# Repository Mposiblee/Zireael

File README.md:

# Zireael keyboard

Zireael is an ergonomic wireless split keyboard with a design bias. Keyboard for Kailh Choc switches based on MINEW MS88SF2 BLE module.

The keyboard is based on Dao Chok BLE. The locations of components on the board have been changed, space for the battery has been added, and the thumb cluster has also been changed.

Inspiration for the keyboard was taken from these keyboards:
- [Dao chok BLE](https://github.com/yumagulovrn/dao-choc-ble) by [Rafael](https://github.com/yumagulovrn) - components pcb
- [Corne-ish Zen](https://lowprokb.ca/products/corne-ish-zen) by [DarrylDH](https://github.com/LOWPROKB) - the idea to create a beautiful case
- [Cornelius](https://geekhack.org/index.php?topic=109741.0) by [foostan](https://github.com/foostan) - keyboard view

## Features

- Hotswapabble
- ZMK firmware
- Low profile
- Top mount
- Choc Spacing (18mm x 17mm)

## Firmware

Latest compiled ZMK firmware for this keyboard can be found here: https://github.com/Mposiblee/zireael-zmk-config/releases/tag/firmware

Source Code: https://github.com/Mposiblee/zireael-zmk-config

## Build guide

https://github.com/Mposiblee/Zireael/blob/main/doc/build_guide.md

## Contacts

Telegram channel: https://t.me/mposibl

My telegram: https://t.me/mposible

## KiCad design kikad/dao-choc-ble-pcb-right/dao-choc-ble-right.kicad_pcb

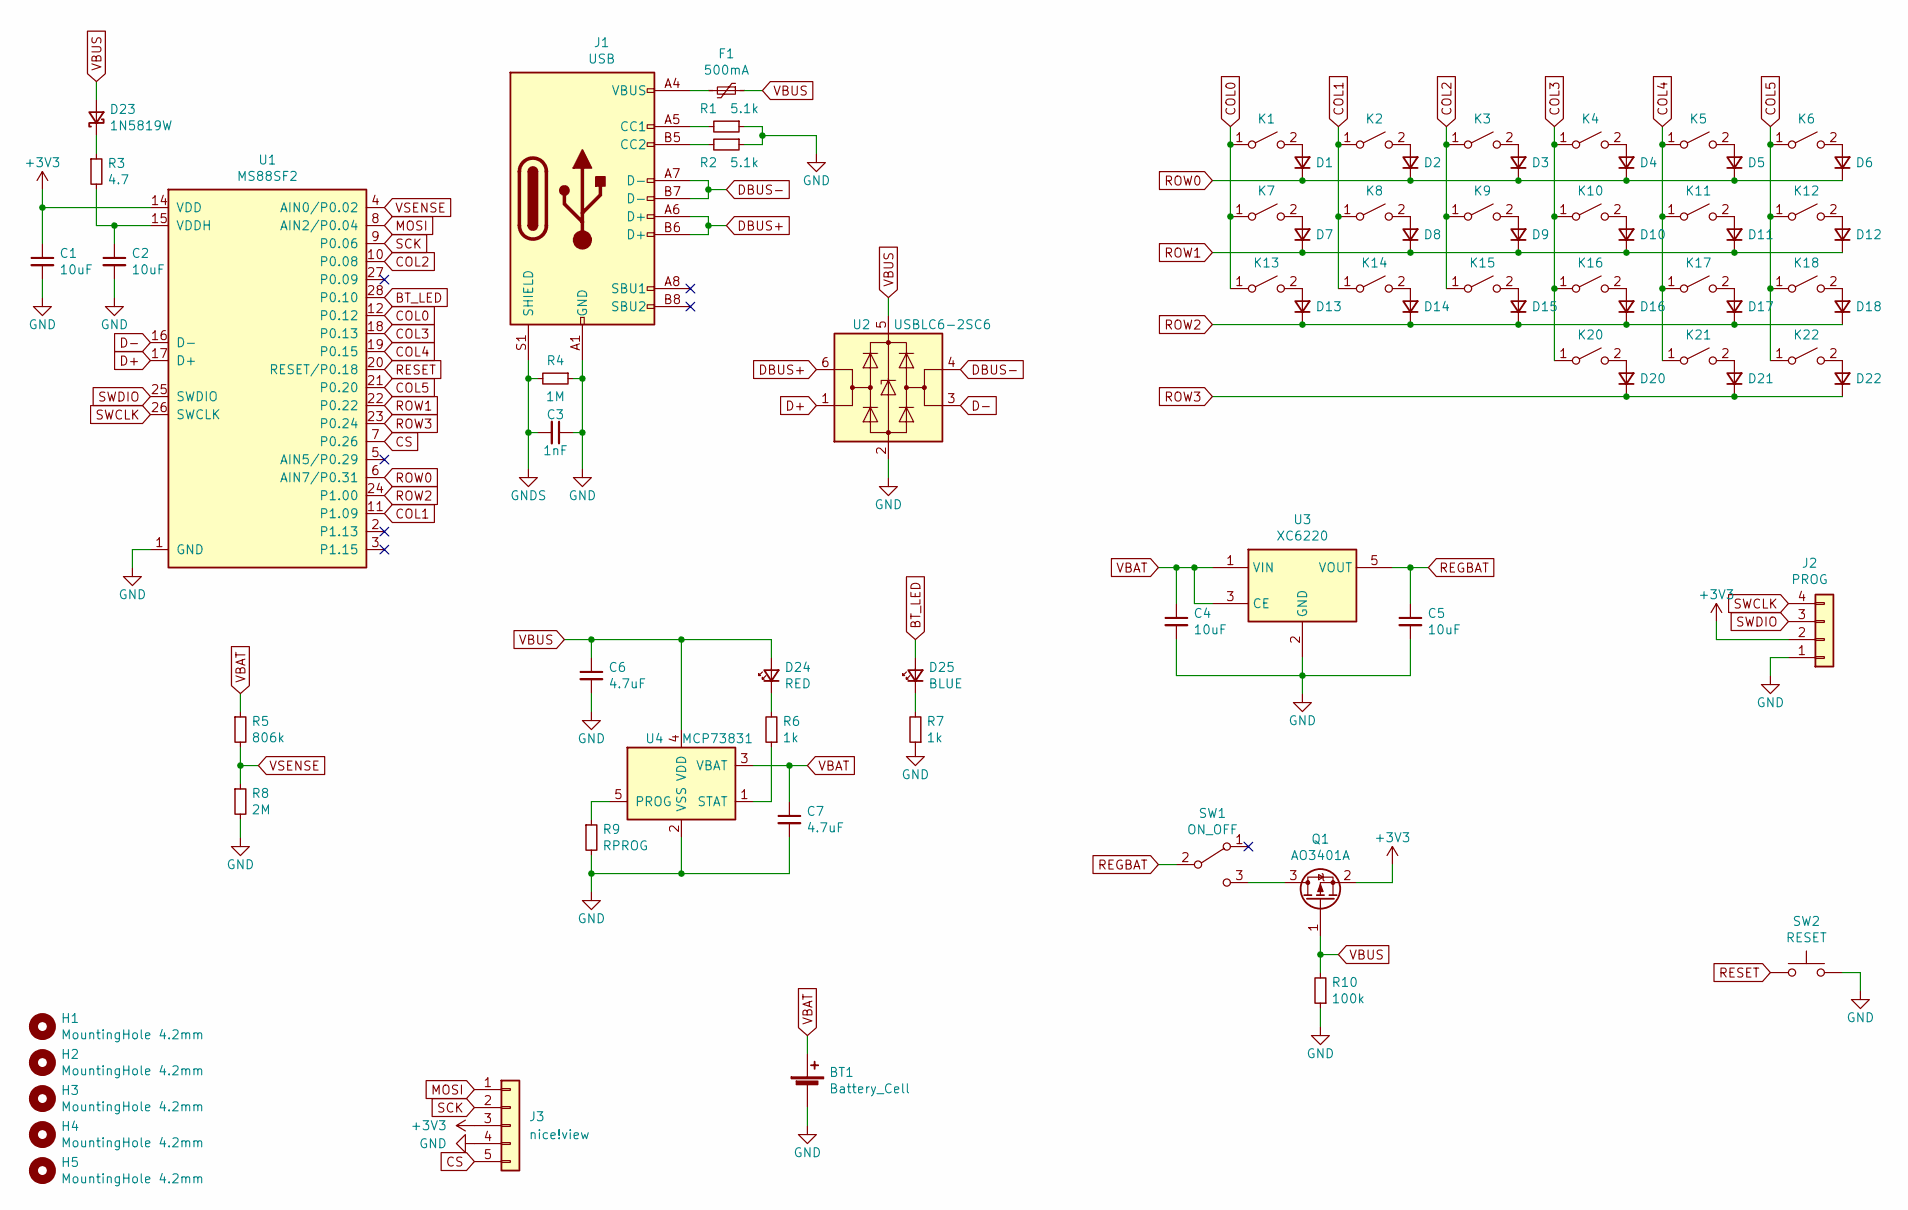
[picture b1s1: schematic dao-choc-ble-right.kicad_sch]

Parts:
BT1: Battery_Cell; Battery
C1, C2, C4, C5: 10uF; C_0603_1608Metric; LCSC C19702
C3: 1nF; C_0603_1608Metric; LCSC C1588
C6, C7: 4.7uF; C_0603_1608Metric; LCSC C19666
D1, D2, D3, D4, D5, D6, D7, D8, D9, D10, D11, D12, D13, D14, D15, D16, D17, D18, D20, D21, D22: 1N4148WS; D_SOD-323; LCSC C57759
D23: 1N5819W; D_SOD-523; LCSC C169540
D24: RED; LED_0603_1608Metric; LCSC C2286
D25: BLUE; LED_0603_1608Metric; LCSC C72041
F1: 500mA; Fuse_1206_3216Metric; LCSC C355568
H1, H2, H3, H4, H5: MountingHole 4.2mm; Hole_4.2mm
J1: USB; USB-C_C168688; LCSC C168688
J2: PROG
J3: nice!view
K1, K2, K3, K4, K5, K6, K7, K8, K9, K10, K11, K12, K13, K14, K15, K16, K17, K18, K20, K21, K22: KEY_SWITCH; Kailh_PG1350_hotswap
Q1: AO3401A; SOT-23; LCSC C15127
R1, R2: 5.1k; R_0603_1608Metric; LCSC C23186
R3: 4.7; R_0603_1608Metric; LCSC C23164
R4: 1M; R_0603_1608Metric; LCSC C22935
R5: 806k; R_0603_1608Metric; LCSC C103828
R6, R7: 1k; R_0603_1608Metric; LCSC C21190
R8: 2M; R_0603_1608Metric; LCSC C22976
R9: RPROG; R_0603_1608Metric; LCSC C22978
R10: 100k; R_0603_1608Metric; LCSC C25803
SW1: ON_OFF; MSK-12C02; LCSC C431541
SW2: RESET; TS-1086E; LCSC C455276
U1: MS88SF2; MINEW_MS88SF2
U2: USBLC6-2SC6; SOT-23-6; LCSC C558442
U3: XC6220; SOT-23-5; LCSC C86534
U4: MCP73831; SOT-23-5; LCSC C14879

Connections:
+3V3: C1.1, J2.2, J3.3, Q1.2 (S), U1.14 (VDD)
BT_LED: D25.2 (A), U1.28 (P0.10)
COL0: K1.1 (A), K7.1 (A), K13.1 (A), U1.12 (P0.12)
COL1: K2.1 (A), K8.1 (A), K14.1 (A), U1.11 (P1.09)
COL2: K3.1 (A), K9.1 (A), K15.1 (A), U1.10 (P0.08)
COL3: K4.1 (A), K10.1 (A), K16.1 (A), K20.1 (A), U1.18 (P0.13)
COL4: K5.1 (A), K11.1 (A), K17.1 (A), K21.1 (A), U1.19 (P0.15)
COL5: K6.1 (A), K12.1 (A), K18.1 (A), K22.1 (A), U1.21 (P0.20)
CS: J3.5, U1.7 (P0.26)
D+: U1.17 (D+), U2.1 (I/O1)
D-: U1.16 (D-), U2.3 (I/O2)
DBUS+: J1.A6 (D+), J1.B6 (D+), U2.6 (I/O1)
DBUS-: J1.A7 (D-), J1.B7 (D-), U2.4 (I/O2)
GND: BT1.2 (-), C1.2, C2.2, C3.1, C4.2, C5.2, C6.2, C7.2, J1.A1 (GND), J1.A12 (GND), J1.B1 (GND), J1.B12 (GND), J2.1, J3.4, R1.1, R2.1, R4.1, R7.1, R8.2, R9.2, R10.1, SW2.2, U1.1 (GND), U1.13 (GND), U2.2 (GND), U3.2 (GND), U4.2 (VSS)
GNDS: C3.2, J1.S1 (SHIELD), R4.2
MOSI: J3.1, U1.8 (AIN2/P0.04)
unnamed: C2.1, R3.2, U1.15 (VDDH)
unnamed: D1.2 (A), K1.2 (B)
unnamed: D2.2 (A), K2.2 (B)
unnamed: D3.2 (A), K3.2 (B)
unnamed: D4.2 (A), K4.2 (B)
unnamed: D5.2 (A), K5.2 (B)
unnamed: D6.2 (A), K6.2 (B)
unnamed: D7.2 (A), K7.2 (B)
unnamed: D8.2 (A), K8.2 (B)
unnamed: D9.2 (A), K9.2 (B)
unnamed: D10.2 (A), K10.2 (B)
unnamed: D11.2 (A), K11.2 (B)
unnamed: D12.2 (A), K12.2 (B)
unnamed: D13.2 (A), K13.2 (B)
unnamed: D14.2 (A), K14.2 (B)
unnamed: D15.2 (A), K15.2 (B)
unnamed: D16.2 (A), K16.2 (B)
unnamed: D17.2 (A), K17.2 (B)
unnamed: D18.2 (A), K18.2 (B)
unnamed: D20.2 (A), K20.2 (B)
unnamed: D21.2 (A), K21.2 (B)
unnamed: D22.2 (A), K22.2 (B)
unnamed: D23.1 (K), R3.1
unnamed: D24.1 (K), R6.2
unnamed: D25.1 (K), R7.2
unnamed: F1.2, J1.A4 (VBUS), J1.A9 (VBUS), J1.B4 (VBUS), J1.B9 (VBUS)
unnamed: J1.A5 (CC1), R1.2
unnamed: J1.B5 (CC2), R2.2
unnamed: Q1.3 (D), SW1.3 (C)
unnamed: R6.1, U4.1 (STAT)
unnamed: R9.1, U4.5 (PROG)
REGBAT: C5.1, SW1.2 (B), U3.5 (VOUT)
RESET: SW2.1, U1.20 (RESET/P0.18)
ROW0: D1.1 (K), D2.1 (K), D3.1 (K), D4.1 (K), D5.1 (K), D6.1 (K), U1.6 (AIN7/P0.31)
ROW1: D7.1 (K), D8.1 (K), D9.1 (K), D10.1 (K), D11.1 (K), D12.1 (K), U1.22 (P0.22)
ROW2: D13.1 (K), D14.1 (K), D15.1 (K), D16.1 (K), D17.1 (K), D18.1 (K), U1.24 (P1.00)
ROW3: D20.1 (K), D21.1 (K), D22.1 (K), U1.23 (P0.24)
SCK: J3.2, U1.9 (P0.06)
SWCLK: J2.4, U1.26 (SWCLK)
SWDIO: J2.3, U1.25 (SWDIO)
VBAT: BT1.1 (+), C4.1, C7.1, R5.1, U3.1 (VIN), U3.3 (CE), U4.3 (VBAT)
VBUS: C6.1, D23.2 (A), D24.2 (A), F1.1, Q1.1 (G), R10.2, U2.5 (VBUS), U4.4 (VDD)
VSENSE: R5.2, R8.1, U1.4 (AIN0/P0.02)

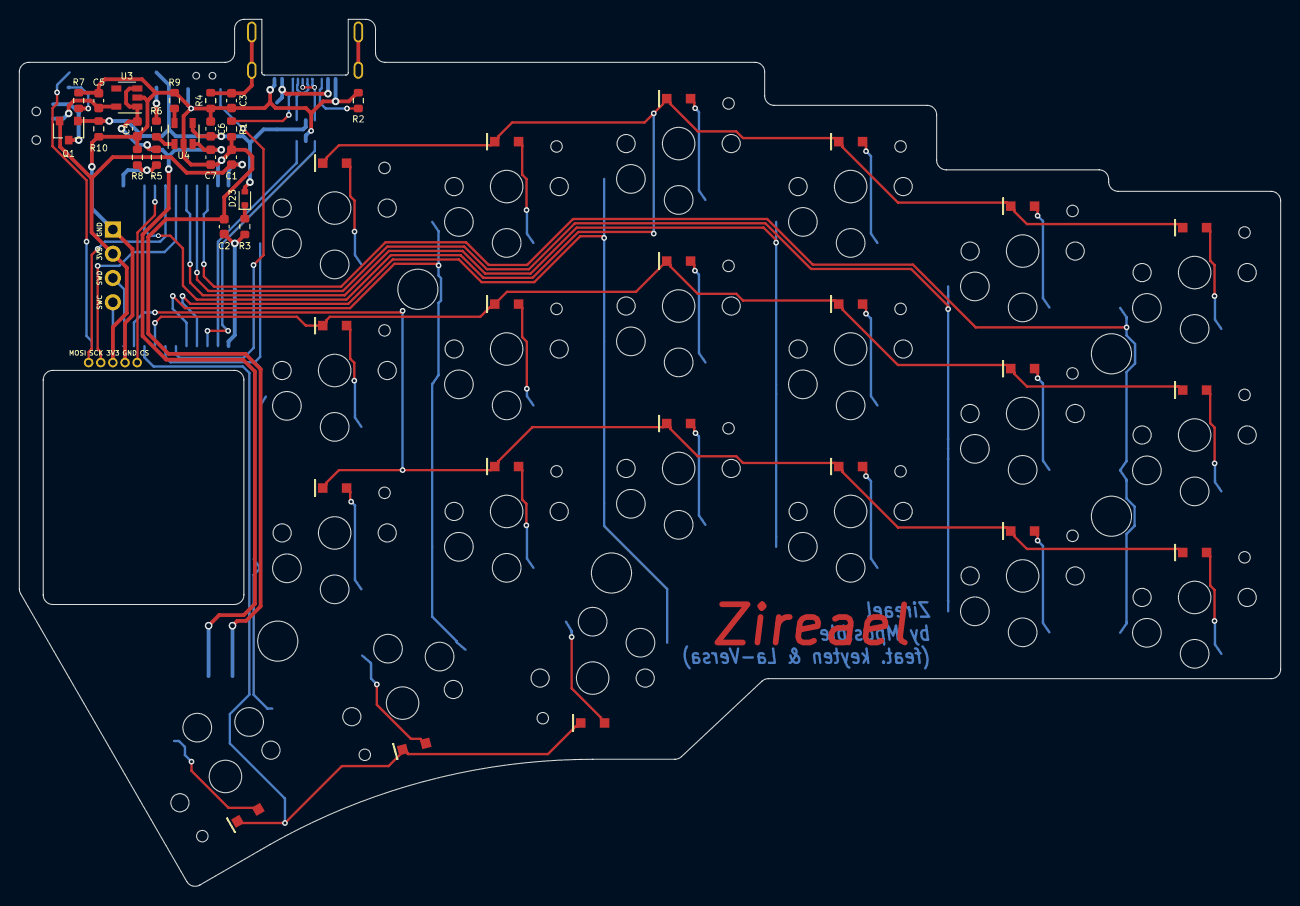
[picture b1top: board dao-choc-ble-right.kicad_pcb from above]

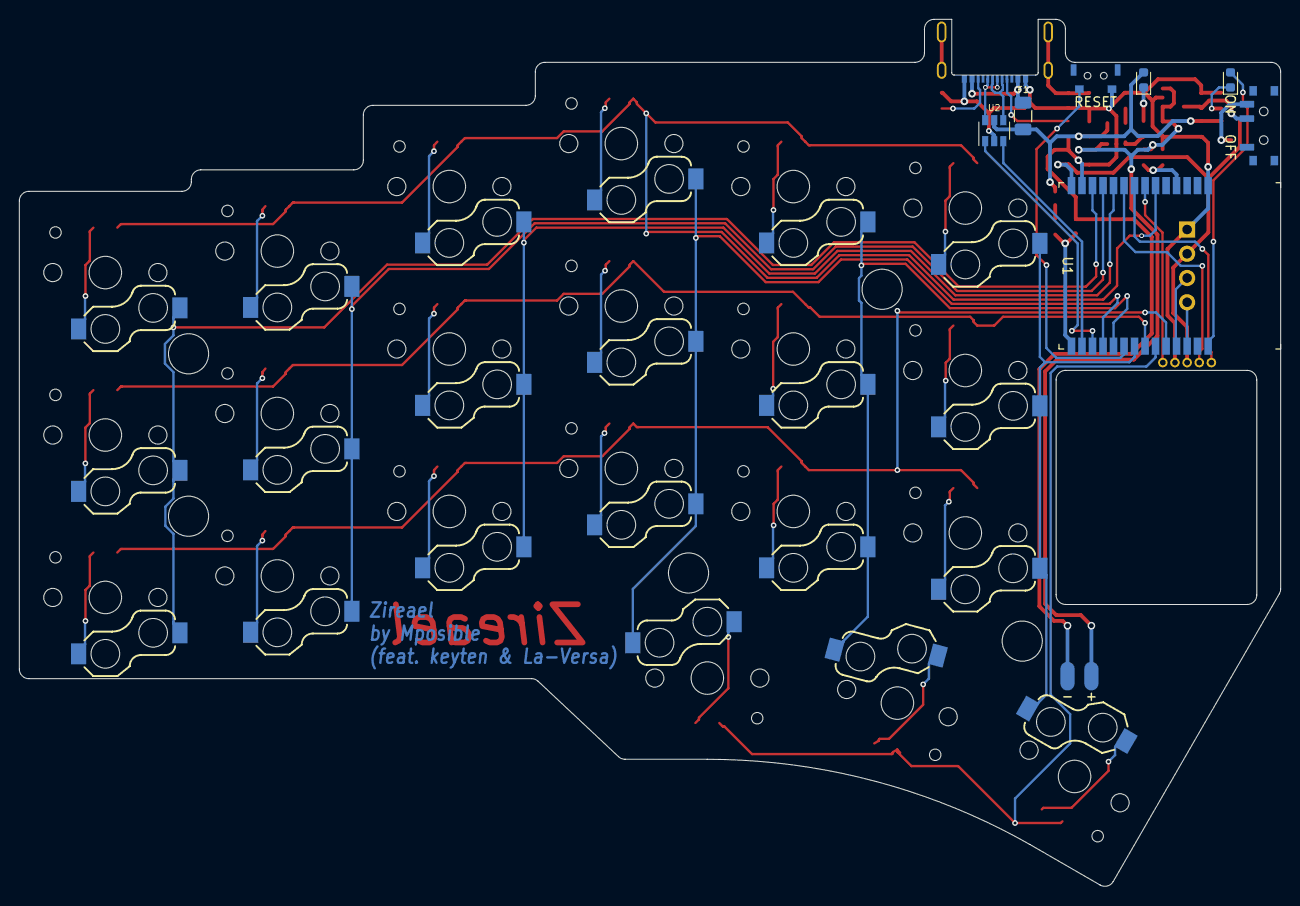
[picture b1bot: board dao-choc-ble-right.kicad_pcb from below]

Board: 2 copper layers, 132.0 x 90.7 mm, 79 parts (9 on the bottom side), 59 nets.

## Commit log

2023-11-07 photos
2023-11-07 Create photos
2023-11-07 Create jpg
2023-11-07 Create fdsa
2023-11-07 Create stl
2023-11-07 Rename stl to sttl
2023-11-07 Create fds
2023-11-07 Create fdsafasd
2023-11-07 Create fdsafadsads
2023-11-07 Create fasfd
2023-11-07 top_left
2023-11-07 Create step
2023-11-07 Rename step to stepp
2023-11-07 Create fdsaf
2023-12-02 Rename buildguide.md to build_guide.md
2023-12-02 Create switches
2023-12-02 Create fdasfsf
2024-01-06 The dimensions have been slightly changed
2024-03-12 Create text
2024-03-12 add zireael clear case
2024-05-23 New version clear case
2024-05-23 New versions switches
2024-05-23 Create f
